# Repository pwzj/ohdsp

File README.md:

# README #

Open Hardware DSP Platform - www.ohdsp.org

Copyright Paul Janicki 2015

Licensed under the TAPR Open Hardware License (www.tapr.org/OHL)

This documentation is distributed WITHOUT ANY EXPRESS OR IMPLIED WARRANTY, INCLUDING OF MERCHANTABILITY, SATISFACTORY QUALITY AND FITNESS FOR A PARTICULAR PURPOSE.

### What is this repository for? ###

* Quick summary

This is an (outdated) open hardware DSP platform repository. 

Please visit www.ohdsp.org and github.com/ohdsp for the latest design files and information.

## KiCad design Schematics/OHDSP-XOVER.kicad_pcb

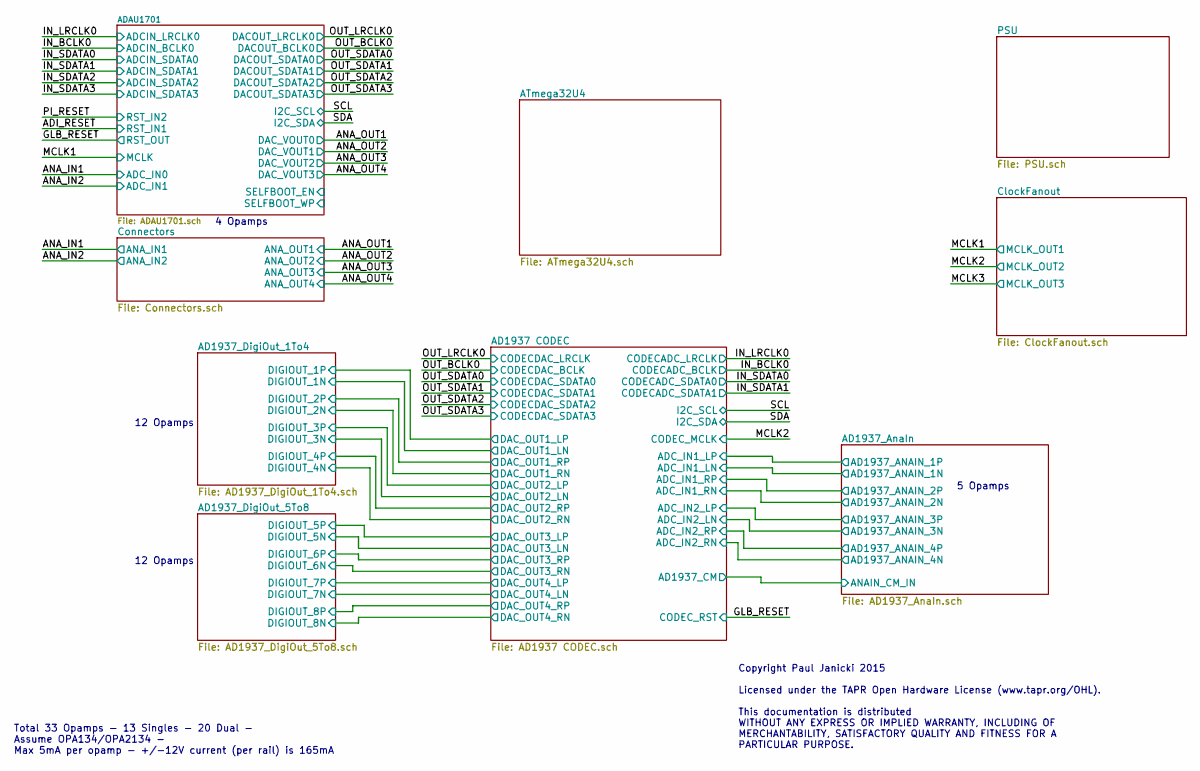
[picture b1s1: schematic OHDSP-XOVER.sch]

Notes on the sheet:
Copyright Paul Janicki 2015 Licensed under the TAPR Open Hardware License (www.tapr.org/OHL). This documentation is distributed WITHOUT ANY EXPRESS OR IMPLIED WARRANTY, INCLUDING OF MERCHANTABILITY, SATISFACTORY QUALITY AND FITNESS FOR A PARTICULAR PURPOSE.
5 Opamps
12 Opamps
4 Opamps
Total 33 Opamps - 13 Singles - 20 Dual - Assume OPA134/OPA2134 - Max 5mA per opamp - +/-12V current (per rail) is 165mA

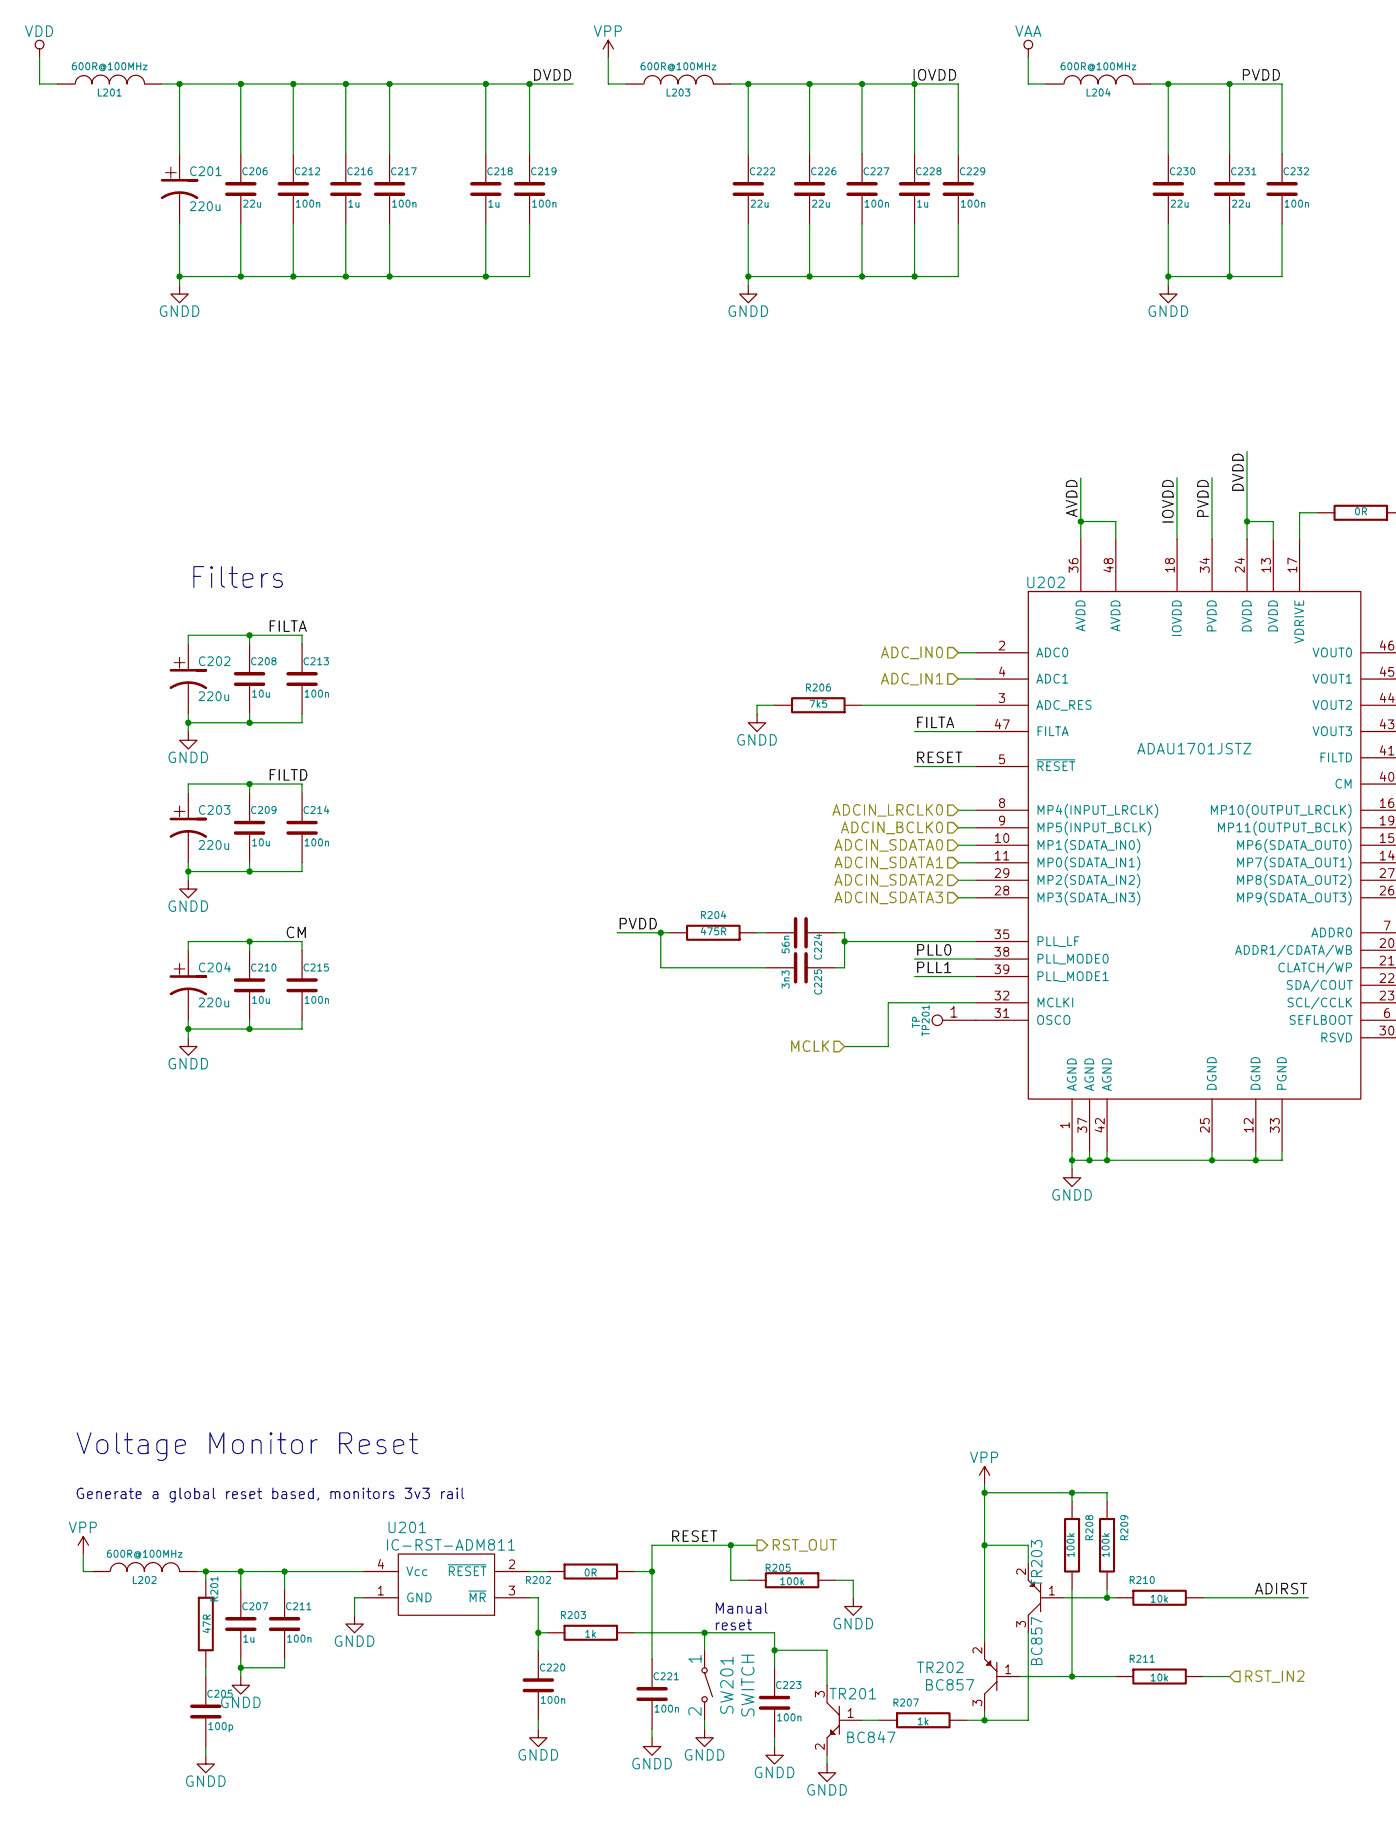
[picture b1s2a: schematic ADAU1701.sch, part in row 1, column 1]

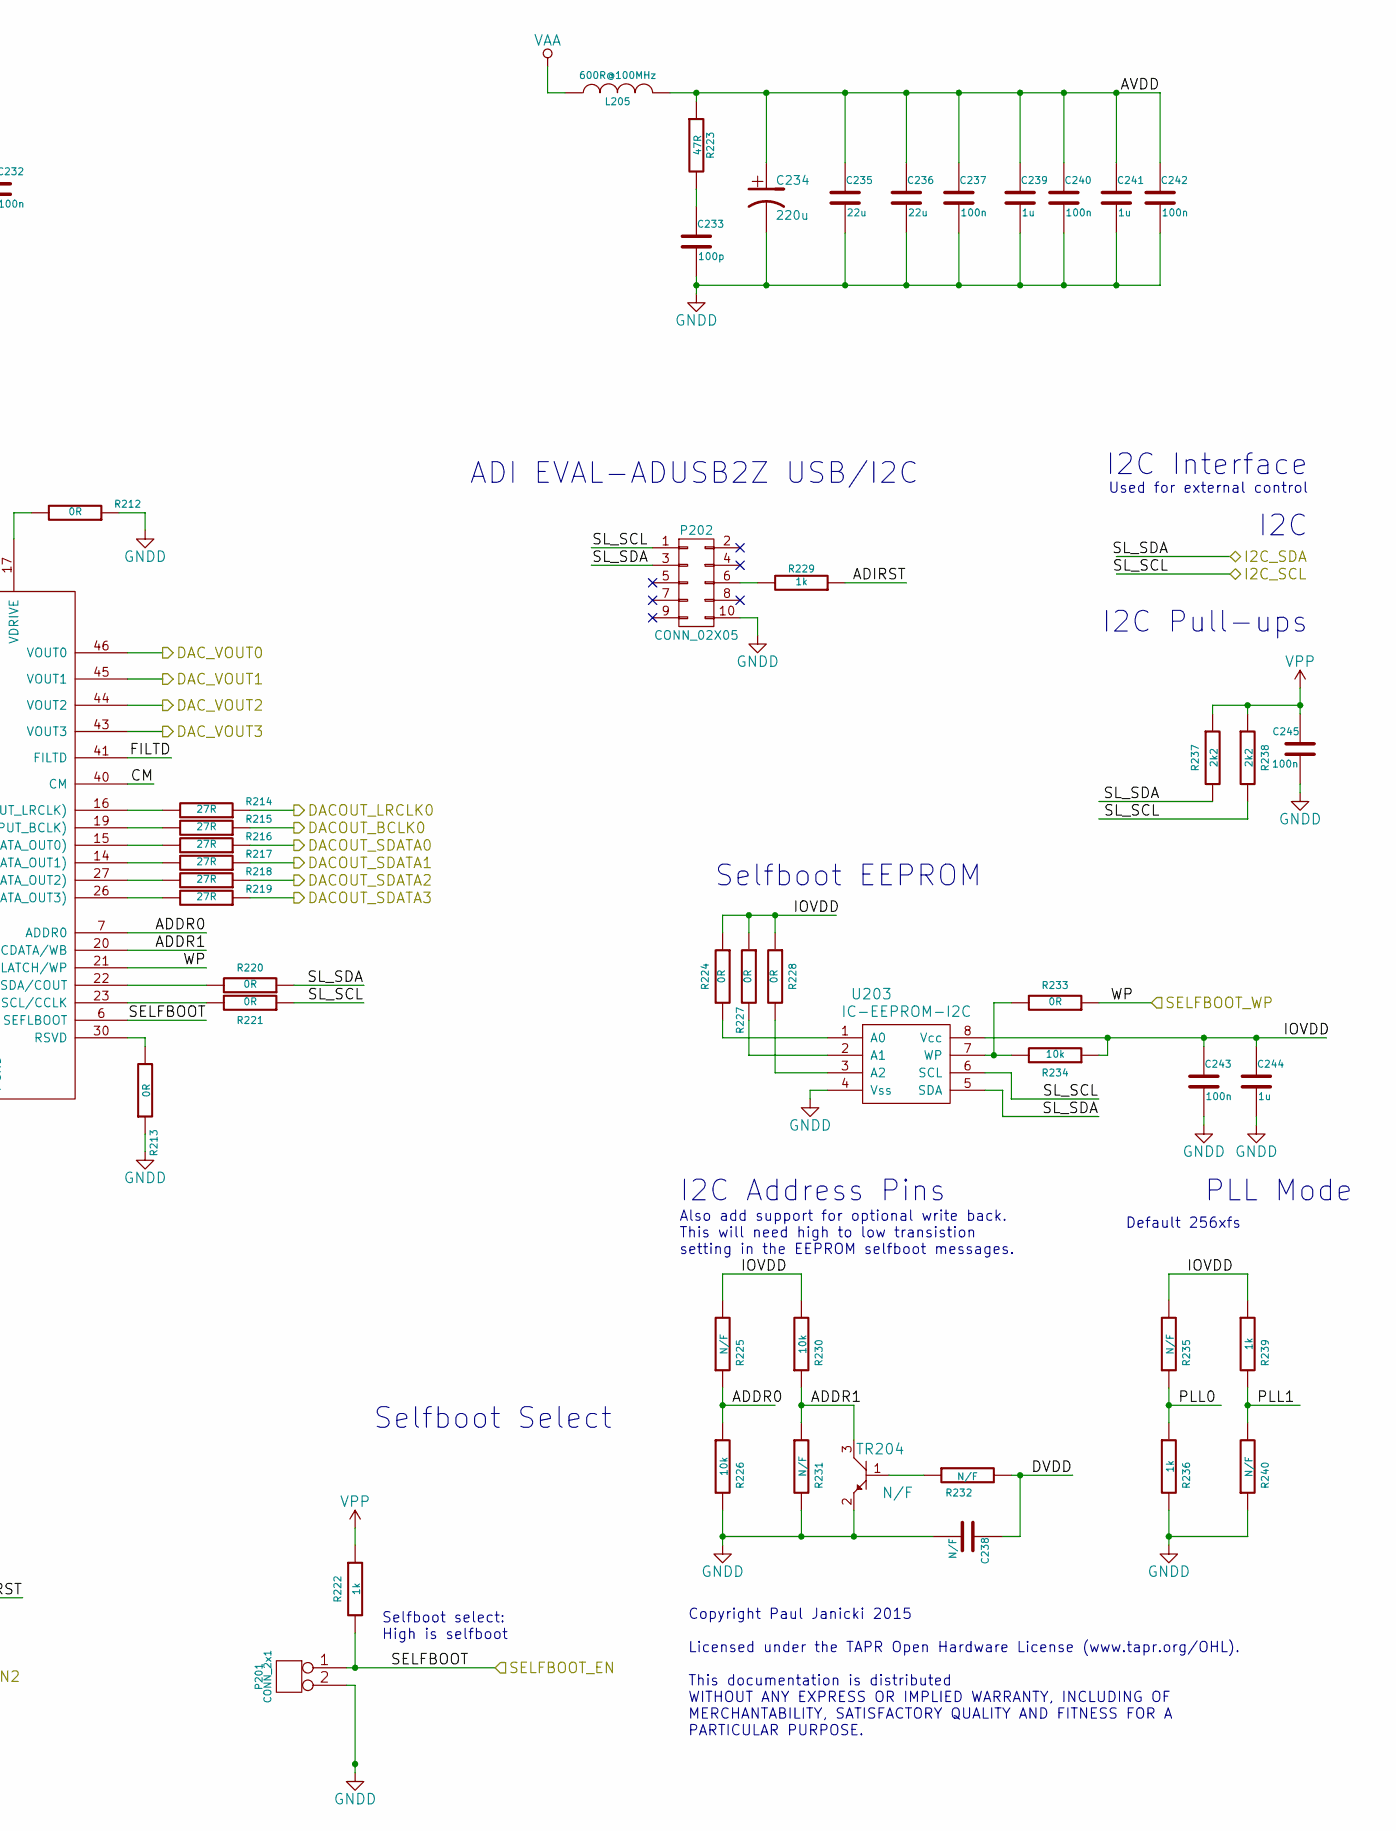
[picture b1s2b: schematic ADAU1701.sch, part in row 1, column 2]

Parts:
C201, C202, C203, C204, C234: 220u; CAP-TH-D6.3mmP2.5mm
C205, C233: 100p; SMD-0805
C206, C222, C226, C230, C231, C235, C236: 22u; SMD-0805
C207, C216, C218, C228, C239, C241, C244: 1u; SMD-0805
C208, C209, C210: 10u; SMD-0805
C211, C212, C213, C214, C215, C217, C219, C220, C221, C223, C227, C229, C232, C237, C240, C242, C243, C245: 100n; SMD-0805
C224: 56n; SMD-0805
C225: 3n3; SMD-0805
C238: N/F; SMD-0805
L201, L202, L203, L204, L205: 600R@100MHz; SMD-0805
P201: CONN_2x1; CONN_SIL_2
P202: CONN_02X05; CONN_DIL_2X5_BOX
R201, R223: 47R; SMD-0805
R202, R212, R213, R220, R221, R224, R227, R228, R233: 0R; SMD-0805
R203, R207, R222, R229, R236, R239: 1k; SMD-0805
R204: 475R; SMD-0805
R205, R208, R209: 100k; SMD-0805
R206: 7k5; SMD-0805
R210, R211, R226, R230, R234: 10k; SMD-0805
R214, R215, R216, R217, R218, R219: 27R; SMD-0805
R225, R231, R232, R235, R240: N/F; SMD-0805
R237, R238: 2k2; SMD-0805
SW201: SWITCH; SW_TACT_SMD
TP201: TP; TP-2mm
TR201: BC847; IC-SOT23
TR202, TR203: BC857; IC-SOT23
TR204: N/F; IC-SOT23
U201: IC-RST-ADM811; IC-SOT143
U202: ADAU1701JSTZ; IC-LQFP48_7x7
U203: IC-EEPROM-I2C; IC_DIP_8

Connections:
/AD1937 CODEC/CODECDAC_BCLK: R215.1; also elsewhere on the board
/AD1937 CODEC/CODECDAC_LRCLK: R214.1; also elsewhere on the board
/AD1937 CODEC/CODECDAC_SDATA0: R216.1; also elsewhere on the board
/AD1937 CODEC/CODECDAC_SDATA1: R217.1; also elsewhere on the board
/AD1937 CODEC/CODECDAC_SDATA2: R218.1; also elsewhere on the board
/AD1937 CODEC/CODECDAC_SDATA3: R219.1; also elsewhere on the board
/AD1937 CODEC/CODEC_RST: C221.1, R202.2, R205.2, U202.5 (~RESET); also elsewhere on the board
/AD1937 CODEC/I2C_SCL: P202.1, R221.1, R238.2, U203.6 (SCL); also elsewhere on the board
/AD1937 CODEC/I2C_SDA: P202.3, R220.1, R237.2, U203.5 (SDA); also elsewhere on the board
/ADAU1701/ADCIN_BCLK0: U202.9 (MP5(INPUT_BCLK)); also elsewhere on the board
/ADAU1701/ADCIN_LRCLK0: U202.8 (MP4(INPUT_LRCLK)); also elsewhere on the board
/ADAU1701/ADCIN_SDATA0: U202.10 (MP1(SDATA_IN0)); also elsewhere on the board
/ADAU1701/ADCIN_SDATA1: U202.11 (MP0(SDATA_IN1)); also elsewhere on the board
/ADAU1701/ADCIN_SDATA2: U202.29 (MP2(SDATA_IN2))
/ADAU1701/ADCIN_SDATA3: U202.28 (MP3(SDATA_IN3))
/ADAU1701/ADC_IN0: U202.2 (ADC0); also elsewhere on the board
/ADAU1701/ADC_IN1: U202.4 (ADC1); also elsewhere on the board
/ADAU1701/ADDR0: R225.1, R226.1, U202.7 (ADDR0)
/ADAU1701/ADDR1: R230.1, R231.1, TR204.3, U202.20 (ADDR1/CDATA/WB)
/ADAU1701/ADIRST: R210.2, R229.1
/ADAU1701/AVDD: C234.1, C235.1, C236.1, C237.1, C239.1, C240.1, C241.1, C242.1, L205.2, R223.1, U202.36 (AVDD), U202.48 (AVDD)
/ADAU1701/CM: C204.1, C210.1, C215.1, U202.40 (CM)
/ADAU1701/DVDD: C201.1, C206.1, C212.1, C216.1, C217.1, C218.1, C219.1, C238.1, L201.2, R232.2, U202.13 (DVDD), U202.24 (DVDD)
/ADAU1701/FILTA: C202.1, C208.1, C213.1, U202.47 (FILTA)
/ADAU1701/FILTD: C203.1, C209.1, C214.1, U202.41 (FILTD)
/ADAU1701/IOVDD: C222.1, C226.1, C227.1, C228.1, C229.1, C243.1, C244.1, L203.2, R224.1, R225.2, R227.1, R228.1, R230.2, R234.1, R235.2, R239.1, U202.18 (IOVDD), U203.8 (Vcc)
/ADAU1701/MCLK: U202.32 (MCLKI); also elsewhere on the board
/ADAU1701/PLL0: R235.1, R236.1, U202.38 (PLL_MODE0)
/ADAU1701/PLL1: R239.2, R240.2, U202.39 (PLL_MODE1)
/ADAU1701/PVDD: C225.2, C230.1, C231.1, C232.1, L204.2, R204.2, U202.34 (PVDD)
/ADAU1701/RST_IN2: R211.2
/ADAU1701/SELFBOOT_EN: P201.1, R222.2, U202.6 (SEFLBOOT)
/ADAU1701/SELFBOOT_WP: R233.1, U202.21 (CLATCH/WP)
/Connectors/ANA_OUT1: U202.46 (VOUT0); also elsewhere on the board
/Connectors/ANA_OUT2: U202.45 (VOUT1); also elsewhere on the board
/Connectors/ANA_OUT3: U202.44 (VOUT2); also elsewhere on the board
/Connectors/ANA_OUT4: U202.43 (VOUT3); also elsewhere on the board
GNDD: C201.2, C202.2, C203.2, C204.2, C205.2, C206.2, C207.2, C208.2, C209.2, C210.2, C211.2, C212.2, C213.2, C214.2, C215.2, C216.2, C217.2, C218.2, C219.2, C220.2, C221.2, C222.2, C223.2, C226.2, C227.2, C228.2, C229.2, C230.2, C231.2, C232.2, C233.2, C234.2, C235.2, C236.2, C237.2, C238.2, C239.2, C240.2, C241.2, C242.2, C243.2, C244.2, C245.2, P201.2, P202.10, R205.1, R206.2, R212.1, R213.1, R226.2, R231.2, R236.2, R240.1, SW201.2, TR201.2, TR204.2, U201.1 (GND), U202.1 (AGND), U202.12 (DGND), U202.25 (DGND), U202.33 (PGND), U202.37 (AGND), U202.42 (AGND), U203.4 (Vss); also elsewhere on the board
unnamed: C205.1, R201.2
unnamed: C207.1, C211.1, L202.2, R201.1, U201.4 (Vcc)
unnamed: C220.1, R203.1, U201.3 (~MR)
unnamed: C223.1, R203.2, SW201.1, TR201.3
unnamed: C224.1, C225.1, U202.35 (PLL_LF)
unnamed: C224.2, R204.1
unnamed: C233.1, R223.2
unnamed: P202.6, R229.2
unnamed: R202.1, U201.2 (~RESET)
unnamed: R206.1, U202.3 (ADC_RES)
unnamed: R207.1, TR201.1
unnamed: R207.2, TR202.3, TR203.3
unnamed: R208.2, R211.1, TR202.1
unnamed: R209.2, R210.1, TR203.1
unnamed: R212.2, U202.17 (VDRIVE)
unnamed: R213.2, U202.30 (RSVD)
unnamed: R214.2, U202.16 (MP10(OUTPUT_LRCLK))
unnamed: R215.2, U202.19 (MP11(OUTPUT_BCLK))
unnamed: R216.2, U202.15 (MP6(SDATA_OUT0))
unnamed: R217.2, U202.14 (MP7(SDATA_OUT1))
unnamed: R218.2, U202.27 (MP8(SDATA_OUT2))
unnamed: R219.2, U202.26 (MP9(SDATA_OUT3))
unnamed: R220.2, U202.22 (SDA/COUT)
unnamed: R221.2, U202.23 (SCL/CCLK)
unnamed: R224.2, U203.1 (A0)
unnamed: R227.2, U203.2 (A1)
unnamed: R228.2, U203.3 (A2)
unnamed: R232.1, TR204.1
unnamed: R233.2, R234.2, U203.7 (WP)
unnamed: TP201.1, U202.31 (OSCO)
VAA: L204.1, L205.1; also elsewhere on the board
VDD: L201.1; also elsewhere on the board
VPP: C245.1, L202.1, L203.1, R208.1, R209.1, R222.1, R237.1, R238.1, TR202.2, TR203.2; also elsewhere on the board

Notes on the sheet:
Selfboot Select
Selfboot select: High is selfboot
Generate a global reset based, monitors 3v3 rail
Voltage Monitor Reset
I2C Pull-ups
I2C
I2C Interface
Used for external control
Manual reset
Copyright Paul Janicki 2015 Licensed under the TAPR Open Hardware License (www.tapr.org/OHL). This documentation is distributed WITHOUT ANY EXPRESS OR IMPLIED WARRANTY, INCLUDING OF MERCHANTABILITY, SATISFACTORY QUALITY AND FITNESS FOR A PARTICULAR PURPOSE.
I2C Address Pins
Selfboot EEPROM
Filters
PLL Mode
Default 256xfs
Also add support for optional write back. This will need high to low transistion setting in the EEPROM selfboot messages.
ADI EVAL-ADUSB2Z USB/I2C

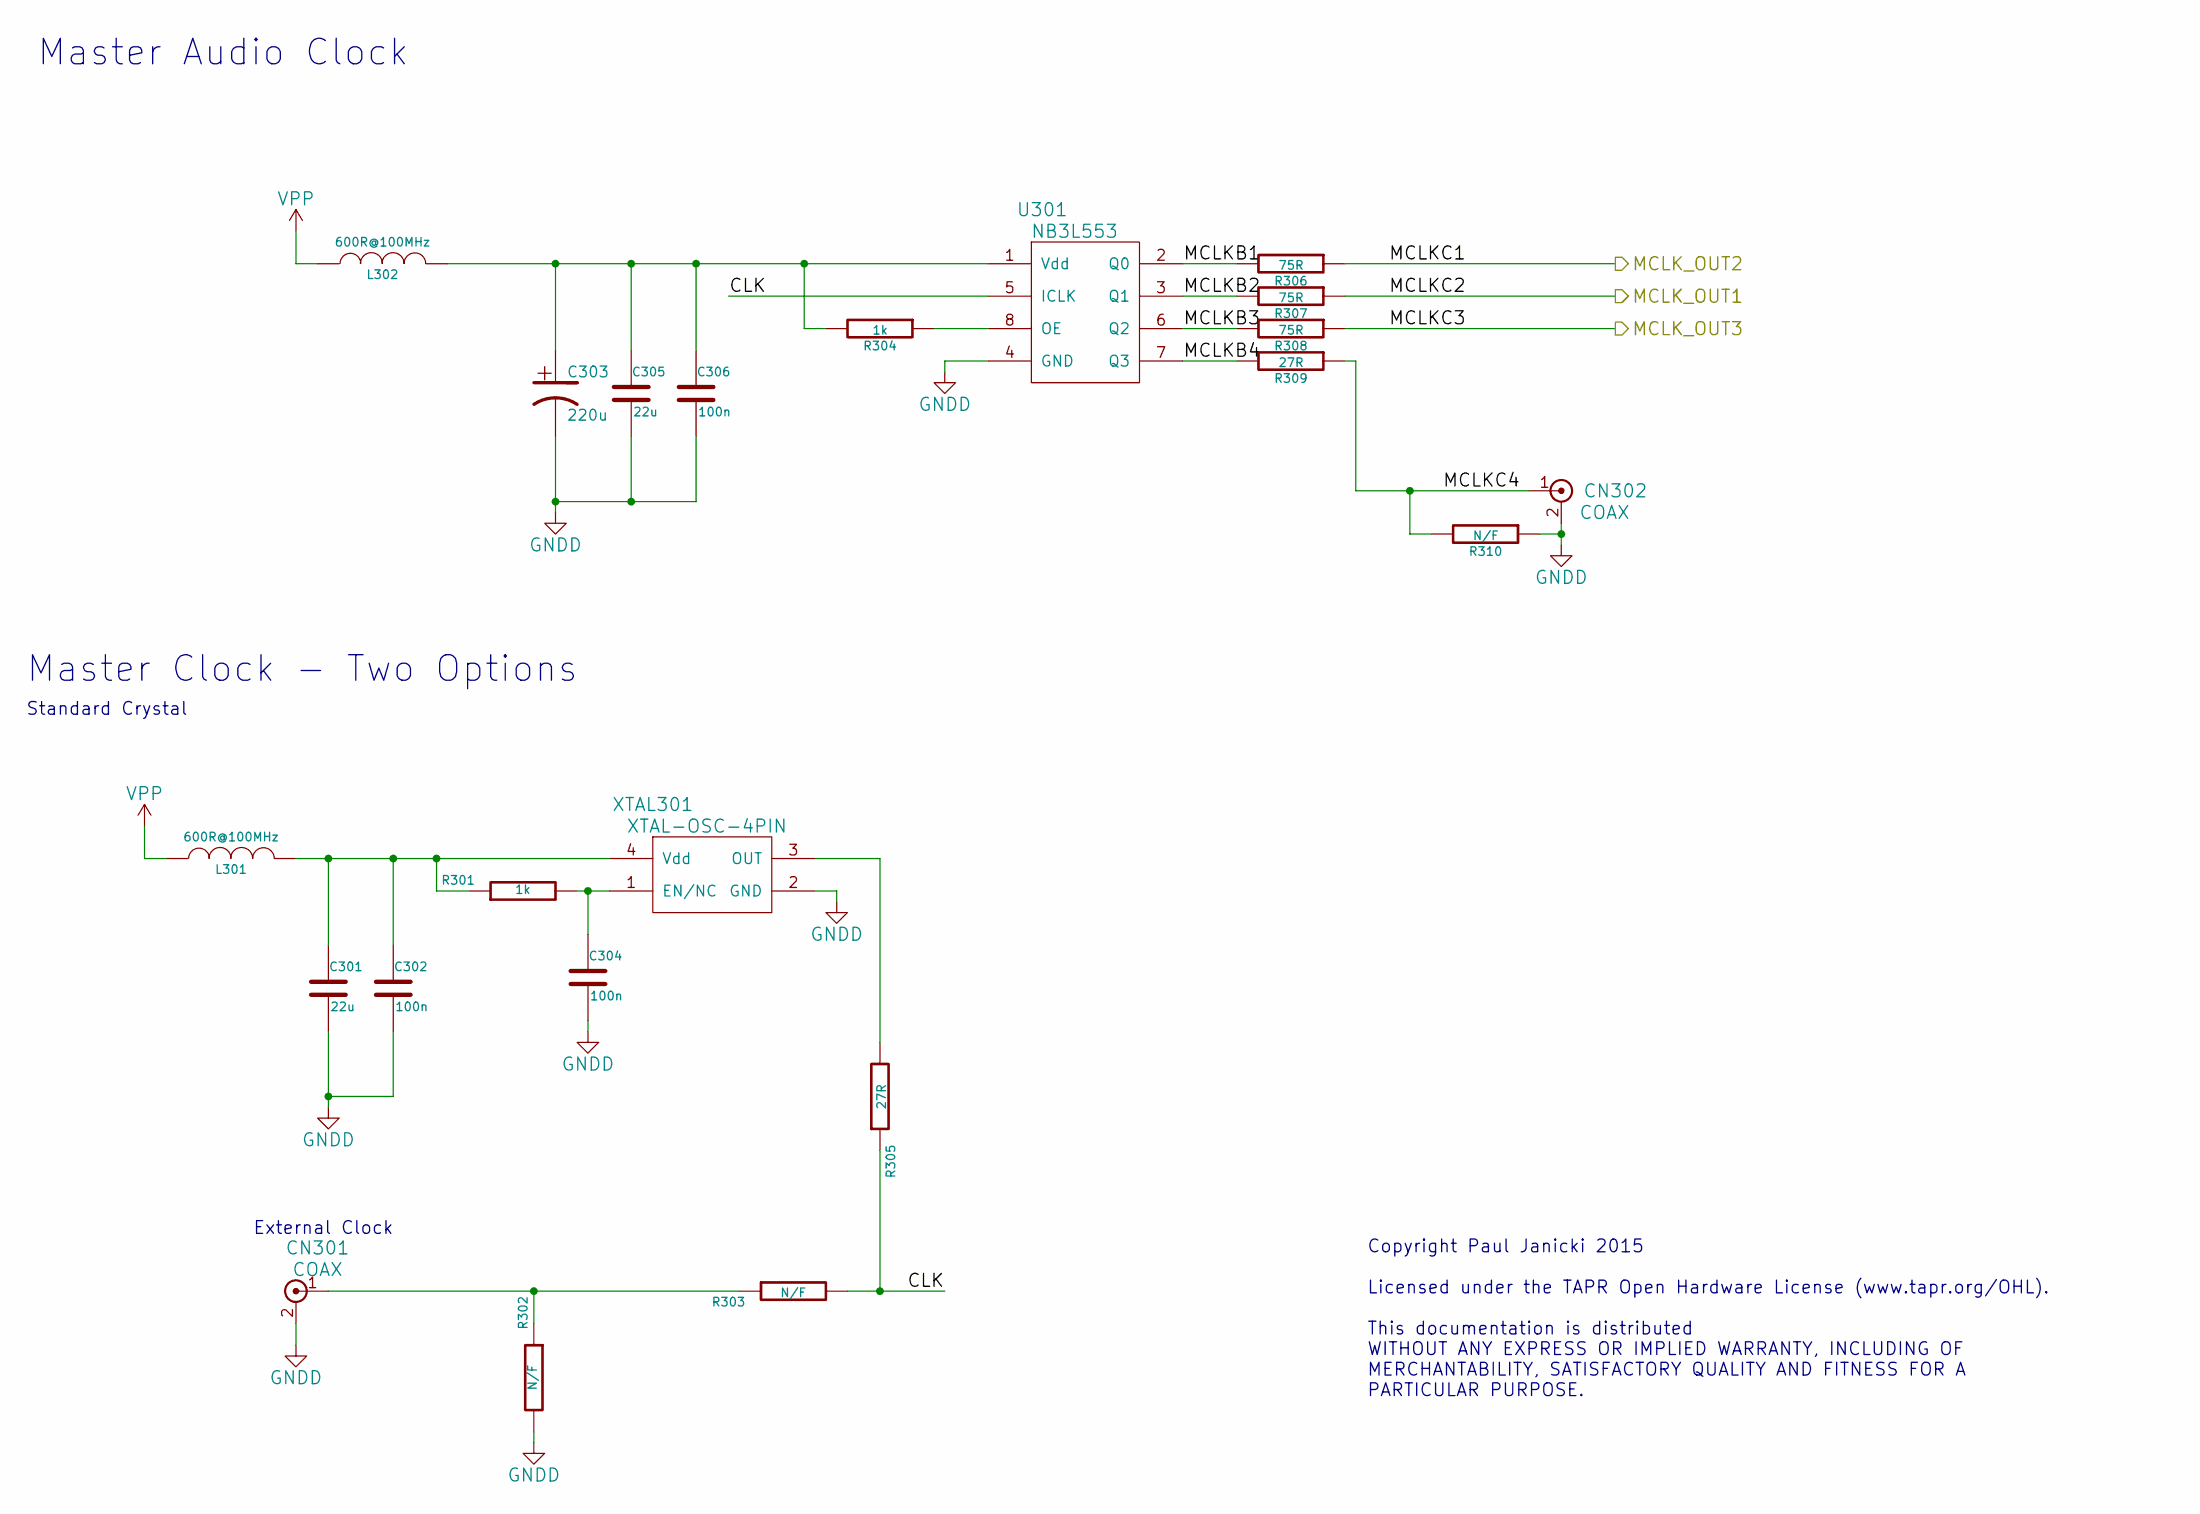
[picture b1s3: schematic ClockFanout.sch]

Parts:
C301, C305: 22u; SMD-0805
C302, C304, C306: 100n; SMD-0805
C303: 220u; CAP-TH-D6.3mmP2.5mm
CN301, CN302: COAX; CONN-RF-UFL
L301, L302: 600R@100MHz; SMD-0805
R301, R304: 1k; SMD-0805
R302, R303, R310: N/F; SMD-0805
R305, R309: 27R; SMD-0805
R306, R307, R308: 75R; SMD-0805
U301: NB3L553; IC_SOIC_8
XTAL301: XTAL-OSC-4PIN; XTAL_8_DIL

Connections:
/AD1937 CODEC/CODEC_MCLK: R306.1; also elsewhere on the board
/ADAU1701/MCLK: R307.1; also elsewhere on the board
/ClockFanout/CLK: R303.2, R305.1, U301.5 (ICLK)
/ClockFanout/MCLKB1: R306.2, U301.2 (Q0)
/ClockFanout/MCLKB2: R307.2, U301.3 (Q1)
/ClockFanout/MCLKB3: R308.2, U301.6 (Q2)
/ClockFanout/MCLKB4: R309.2, U301.7 (Q3)
/ClockFanout/MCLKC4: CN302.1, R309.1, R310.2
/ClockFanout/MCLK_OUT3: R308.1
GNDD: C301.2, C302.2, C303.2, C304.2, C305.2, C306.2, CN301.2, CN302.2, R302.2, R310.1, U301.4 (GND), XTAL301.2 (GND); also elsewhere on the board
unnamed: C301.1, C302.1, L301.2, R301.1, XTAL301.4 (Vdd)
unnamed: C303.1, C305.1, C306.1, L302.2, R304.2, U301.1 (Vdd)
unnamed: C304.1, R301.2, XTAL301.1 (EN/NC)
unnamed: CN301.1, R302.1, R303.1
unnamed: R304.1, U301.8 (OE)
unnamed: R305.2, XTAL301.3 (OUT)
VPP: L301.1, L302.1; also elsewhere on the board

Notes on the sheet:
Master Audio Clock
Copyright Paul Janicki 2015 Licensed under the TAPR Open Hardware License (www.tapr.org/OHL). This documentation is distributed WITHOUT ANY EXPRESS OR IMPLIED WARRANTY, INCLUDING OF MERCHANTABILITY, SATISFACTORY QUALITY AND FITNESS FOR A PARTICULAR PURPOSE.
Master Clock - Two Options
Standard Crystal
External Clock

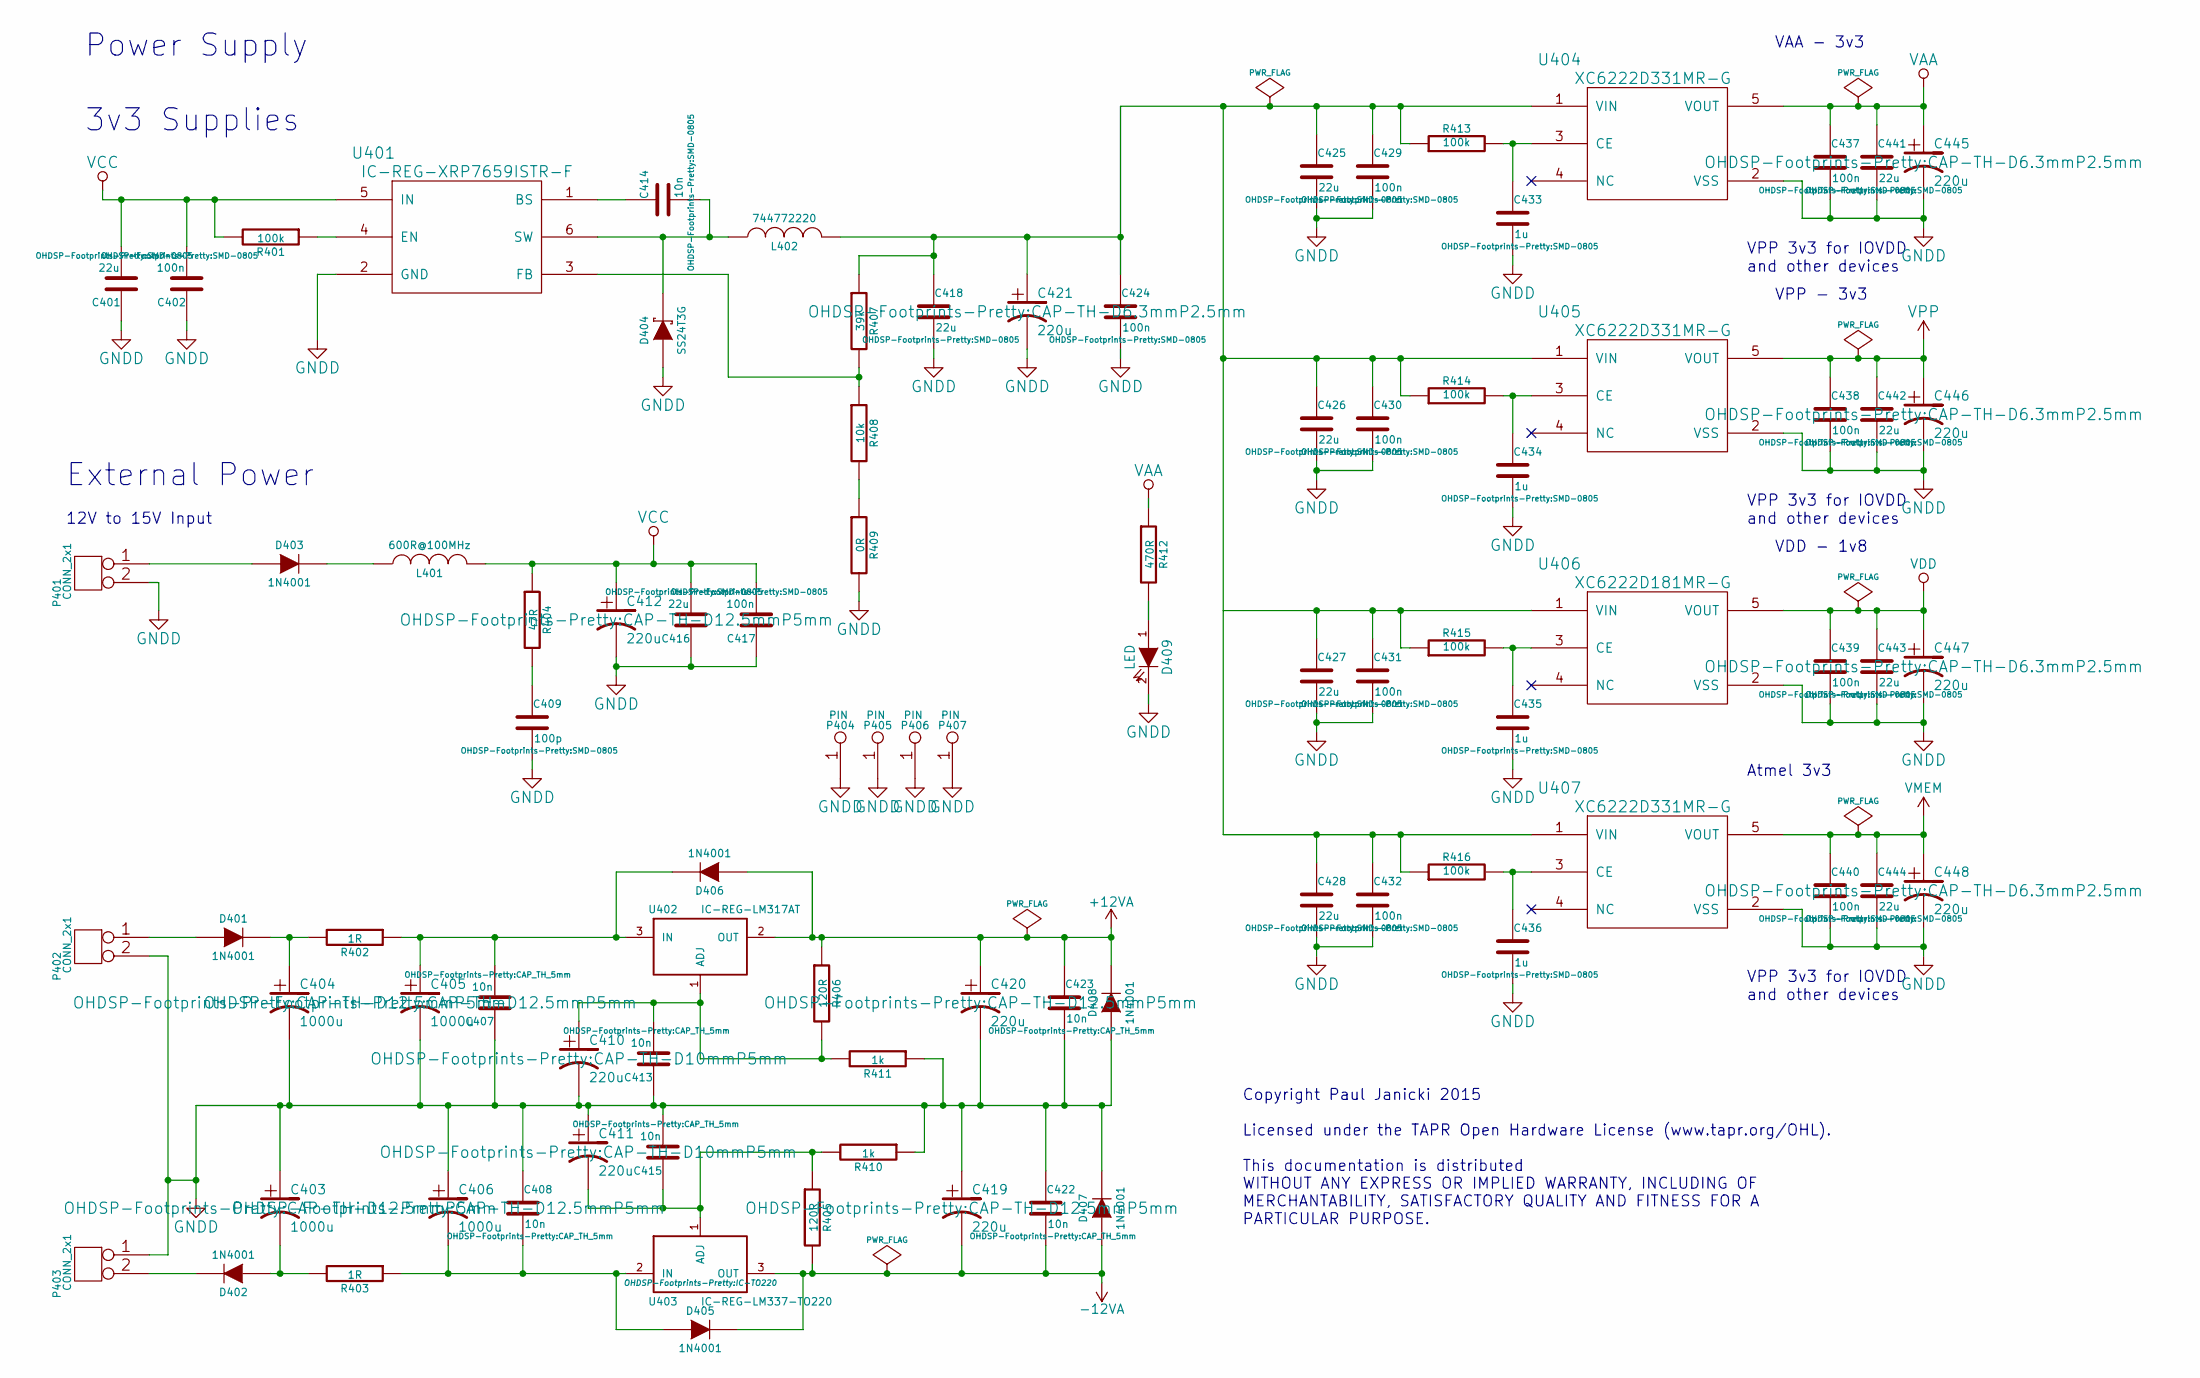
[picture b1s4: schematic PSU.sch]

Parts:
C401, C416, C418, C425, C426, C427, C428, C441, C442, C443, C444: 22u; SMD-0805
C402, C417, C424, C429, C430, C431, C432, C437, C438, C439, C440: 100n; SMD-0805
C403, C404, C405, C406: 1000u; CAP-TH-D12.5mmP5mm
C407, C408, C413, C415, C422, C423: 10n; CAP_TH_5mm
C409: 100p; SMD-0805
C410, C411: 220u; CAP-TH-D10mmP5mm
C412, C419, C420: 220u; CAP-TH-D12.5mmP5mm
C414: 10n; SMD-0805
C421, C445, C446, C447, C448: 220u; CAP-TH-D6.3mmP2.5mm
C433, C434, C435, C436: 1u; SMD-0805
D401, D402, D403, D405, D406, D407, D408: 1N4001; DIODE-DO-41
D404: SS24T3G; DIODE-SMB
D409: LED; SMD-1206
L401: 600R@100MHz; SMD-0805
L402: 744772220; PASSIVE-TH-IND-WURTH-5mm
P401, P402, P403: CONN_2x1; CONN-SCREW-2WAY-5mm-5.08mm
P404, P405, P406, P407: PIN; MNT_HOLE_2.5mm
R401, R413, R414, R415, R416: 100k; SMD-0805
R402, R403: 1R; SMD-0805
R404: 47R; SMD-0805
R405, R406: 120R; SMD-0805
R407: 39k; SMD-0805
R408: 10k; SMD-0805
R409: 0R; SMD-0805
R410, R411: 1k; SMD-0805
R412: 470R; SMD-0805
U401: IC-REG-XRP7659ISTR-F; IC-SOT23-6
U402: IC-REG-LM317AT; IC-TO220
U403: IC-REG-LM337-TO220; IC-TO220
U404, U405, U407: XC6222D331MR-G; IC-SOT25
U406: XC6222D181MR-G; IC-SOT25

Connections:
+12VA: C420.1, C423.1, D406.1 (A), D408.2 (K), R406.1, U402.2 (OUT); also elsewhere on the board
-12VA: C419.2, C422.2, D405.2 (K), D407.1 (A), R405.2, U403.3 (OUT); also elsewhere on the board
GNDD: C401.1, C402.1, C403.1, C404.2, C405.2, C406.1, C407.1, C408.1, C409.2, C410.2, C411.1, C412.2, C413.1, C415.2, C416.1, C417.1, C418.2, C419.1, C420.2, C421.2, C422.1, C423.2, C424.2, C425.2, C426.2, C427.2, C428.2, C429.2, C430.2, C431.2, C432.2, C433.2, C434.2, C435.2, C436.2, C437.2, C438.2, C439.2, C440.2, C441.2, C442.2, C443.2, C444.2, C445.2, C446.2, C447.2, C448.2, D404.1 (A), D407.2 (K), D408.1 (A), D409.2 (K), P401.2, P402.2, P403.1, P404.1, P405.1, P406.1, P407.1, R409.2, R410.1, R411.1, U401.2 (GND), U404.2 (VSS), U405.2 (VSS), U406.2 (VSS), U407.2 (VSS); also elsewhere on the board
unnamed: C403.2, D402.1 (A), R403.2
unnamed: C404.1, D401.2 (K), R402.2
unnamed: C405.1, C407.2, D406.2 (K), R402.1, U402.3 (IN)
unnamed: C406.2, C408.2, D405.1 (A), R403.1, U403.2 (IN)
unnamed: C409.1, R404.2
unnamed: C410.1, C413.2, R406.2, R411.2, U402.1 (ADJ)
unnamed: C411.2, C415.1, R405.1, R410.2, U403.1 (ADJ)
unnamed: C414.1, U401.1 (BS)
unnamed: C414.2, D404.2 (K), L402.1, U401.6 (SW)
unnamed: C418.1, C421.1, C424.1, C425.1, C426.1, C428.1, C429.1, C430.1, C432.1, L402.2, R407.1, R413.1, R414.1, R416.1, U404.1 (VIN), U405.1 (VIN), U407.1 (VIN)
unnamed: C427.1, C431.1, R415.1, U406.1 (VIN)
unnamed: C433.1, R413.2, U404.3 (CE)
unnamed: C434.1, R414.2, U405.3 (CE)
unnamed: C435.1, R415.2, U406.3 (CE)
unnamed: C436.1, R416.2, U407.3 (CE)
unnamed: D401.1 (A), P402.1
unnamed: D402.2 (K), P403.2
unnamed: D403.1 (A), P401.1
unnamed: D403.2 (K), L401.1
unnamed: D409.1 (A), R412.2
unnamed: R401.1, U401.4 (EN)
unnamed: R407.2, R408.1, U401.3 (FB)
unnamed: R408.2, R409.1
VAA: C437.1, C441.1, C445.1, R412.1, U404.5 (VOUT); also elsewhere on the board
VCC: C401.2, C402.2, C412.1, C416.2, C417.2, L401.2, R401.2, R404.1, U401.5 (IN)
VDD: C439.1, C443.1, C447.1, U406.5 (VOUT); also elsewhere on the board
VMEM: C440.1, C444.1, C448.1, U407.5 (VOUT); also elsewhere on the board
VPP: C438.1, C442.1, C446.1, U405.5 (VOUT); also elsewhere on the board

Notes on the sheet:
Power Supply
3v3 Supplies
VAA - 3v3
VPP 3v3 for IOVDD and other devices
External Power
Copyright Paul Janicki 2015 Licensed under the TAPR Open Hardware License (www.tapr.org/OHL). This documentation is distributed WITHOUT ANY EXPRESS OR IMPLIED WARRANTY, INCLUDING OF MERCHANTABILITY, SATISFACTORY QUALITY AND FITNESS FOR A PARTICULAR PURPOSE.
VDD - 1v8
Atmel 3v3
VPP - 3v3
12V to 15V Input
